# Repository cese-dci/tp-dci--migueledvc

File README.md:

#tp-dci--migueledvc

Placa adaptadora de señales de radar
====================================

+ El presente documento presenta la idea de un circuito adaptador de señales típicas de un radar.

+ No se especifica un modelo de radar en particular.

+ El circuíto es parte del desarrollo de un procesador de radar con tecnología FPGA-SoC. (ADC-SoC de Terasic)

+ Se utiliza para esta placa licencia "BSD 3-clause"

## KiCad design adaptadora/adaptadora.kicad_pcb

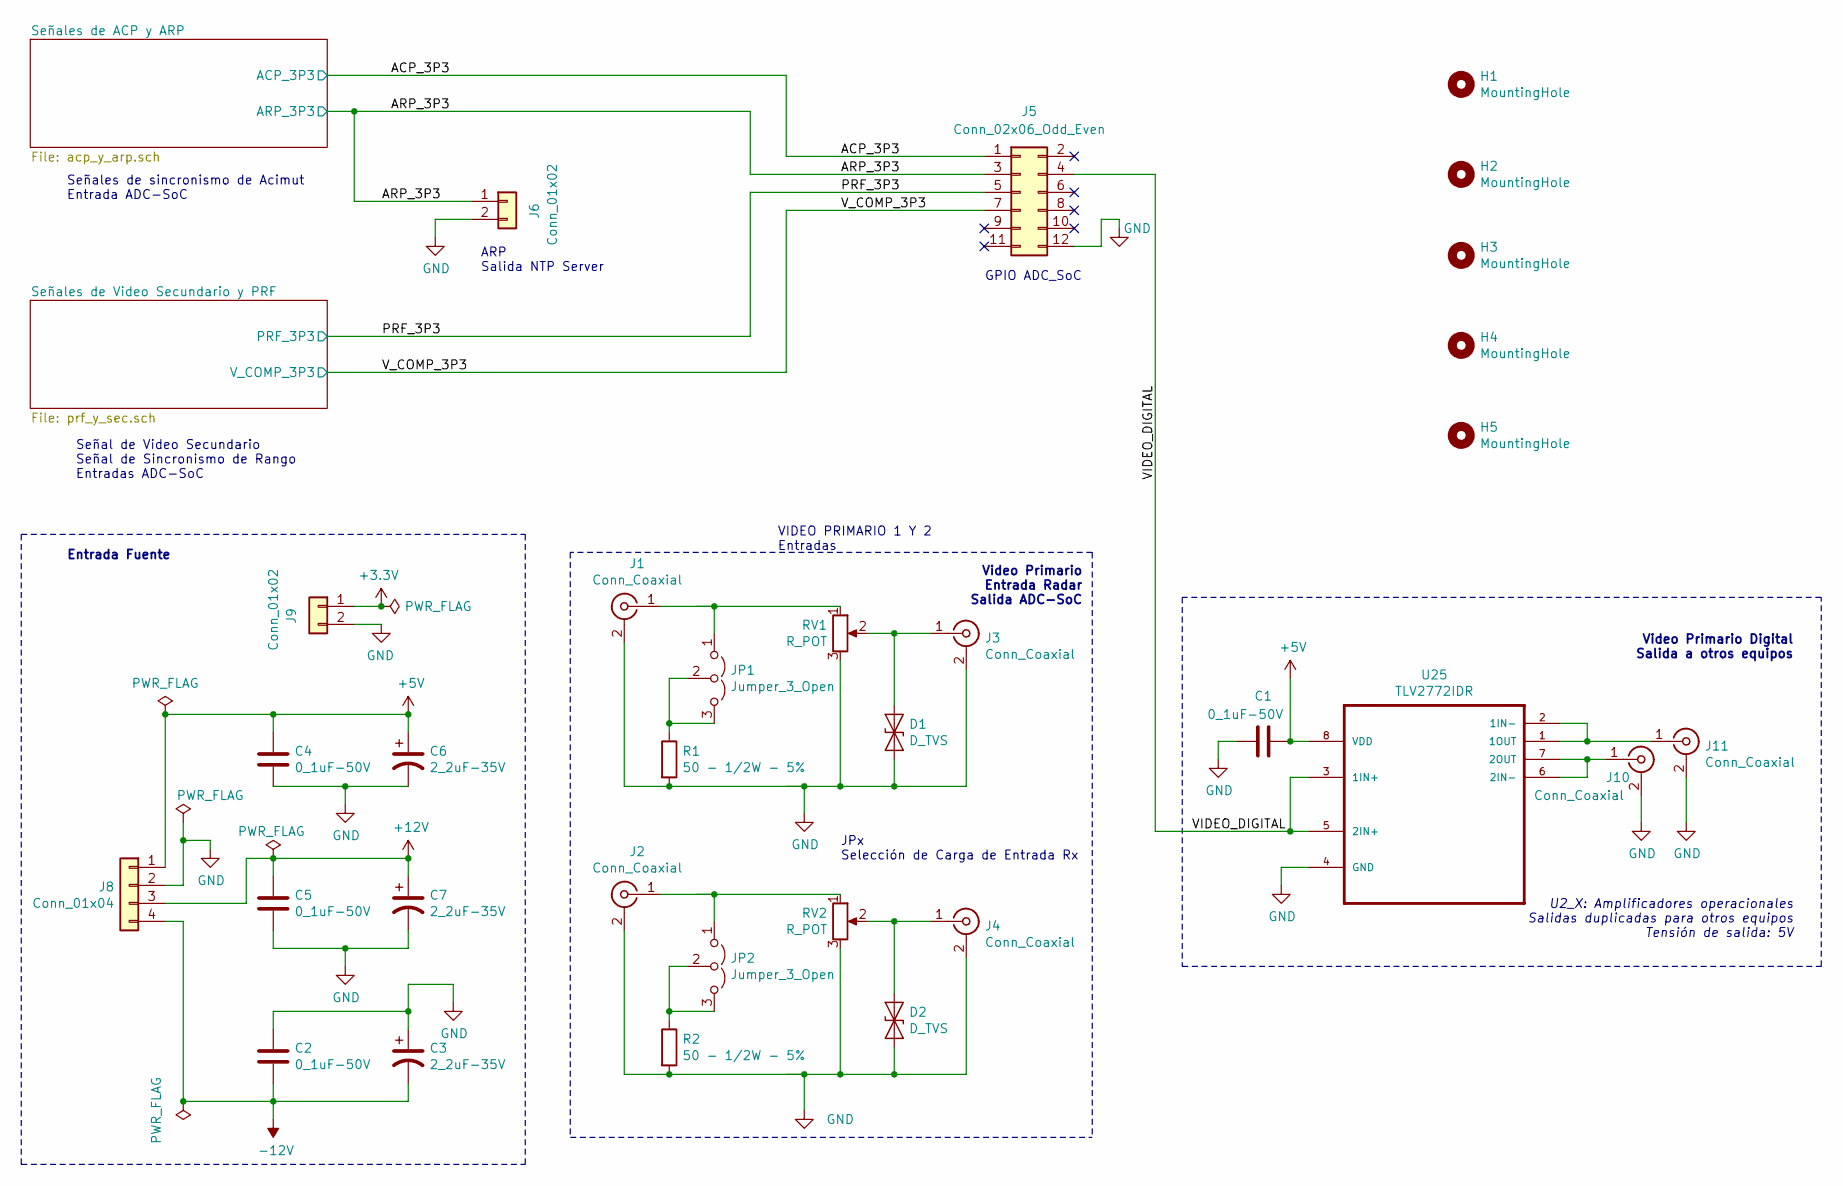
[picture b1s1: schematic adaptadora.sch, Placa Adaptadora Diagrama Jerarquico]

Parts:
C1, C2, C4, C5: 0_1uF-50V; C_0805_2012Metric
C3, C6, C7: 2_2uF-35V; CP_EIA-6032-28_Kemet-C
D1, D2: D_TVS; D_DO-15_P10.16mm_Horizontal
H1, H2, H3, H4, H5: MountingHole; MountingHole_3.2mm_M3_Pad
J1, J2, J3, J4, J10, J11: Conn_Coaxial; SMA_Amphenol_901-144_Vertical
J5: Conn_02x06_Odd_Even; PinHeader_2x06_P2.54mm_Horizontal
J6, J9: Conn_01x02; PinHeader_1x02_P2.54mm_Vertical
J8: Conn_01x04; PinHeader_1x04_P2.54mm_Vertical
JP1, JP2: Jumper_3_Open; PinHeader_1x03_P2.54mm_Vertical
R1, R2: 50 - 1/2W - 5%; R_Axial_DIN0414_L11.9mm_D4.5mm_P15.24mm_Horizontal
RV1, RV2: R_POT; Potentiometer_Bourns_3296W_Vertical
U25: TLV2772IDR; SOIC-8_3.9x4.9mm_P1.27mm

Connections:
+3V3: J9.1; also elsewhere on the board
+5V: C1.1, C4.1, C6.1, J8.1, U25.8 (VDD); also elsewhere on the board
+12V: C5.1, C7.1, J8.3; also elsewhere on the board
-12V: C2.2, C3.2, J8.4; also elsewhere on the board
/ACP_3P3: J5.9; also elsewhere on the board
/PRF_3P3: J5.5; also elsewhere on the board
GND: C1.2, C2.1, C3.1, C4.2, C5.2, C6.2, C7.2, D1.2 (A2), D2.2 (A2), J1.2 (Ext), J2.2 (Ext), J3.2 (Ext), J4.2 (Ext), J5.12, J6.2, J8.2, J9.2, J10.2 (Ext), J11.2 (Ext), R1.2, R2.2, RV1.3, RV2.3, U25.4 (GND); also elsewhere on the board
unnamed: D1.1 (A1), J3.1 (In), RV1.2
unnamed: D2.1 (A1), J4.1 (In), RV2.2
unnamed: J1.1 (In), JP1.1 (A), RV1.1
unnamed: J2.1 (In), JP2.1 (A), RV2.1
unnamed: J10.1 (In), U25.6 (2IN-), U25.7 (2OUT)
unnamed: J11.1 (In), U25.1 (1OUT), U25.2 (1IN-)
unnamed: JP1.2 (C), JP1.3 (B), R1.1
unnamed: JP2.2 (C), JP2.3 (B), R2.1

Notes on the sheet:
VIDEO PRIMARIO 1 Y 2 Entradas
Video Primario Entrada Radar Salida ADC-SoC
Señales de sincronismo de Acimut Entrada ADC-SoC
GPIO ADC_SoC
ARP Salida NTP Server
Video Primario Digital Salida a otros equipos
Entrada Fuente
Señal de Video Secundario Señal de Sincronismo de Rango Entradas ADC-SoC
U2_X: Amplificadores operacionales Salidas duplicadas para otros equipos Tensión de salida: 5V
JPx Selección de Carga de Entrada Rx

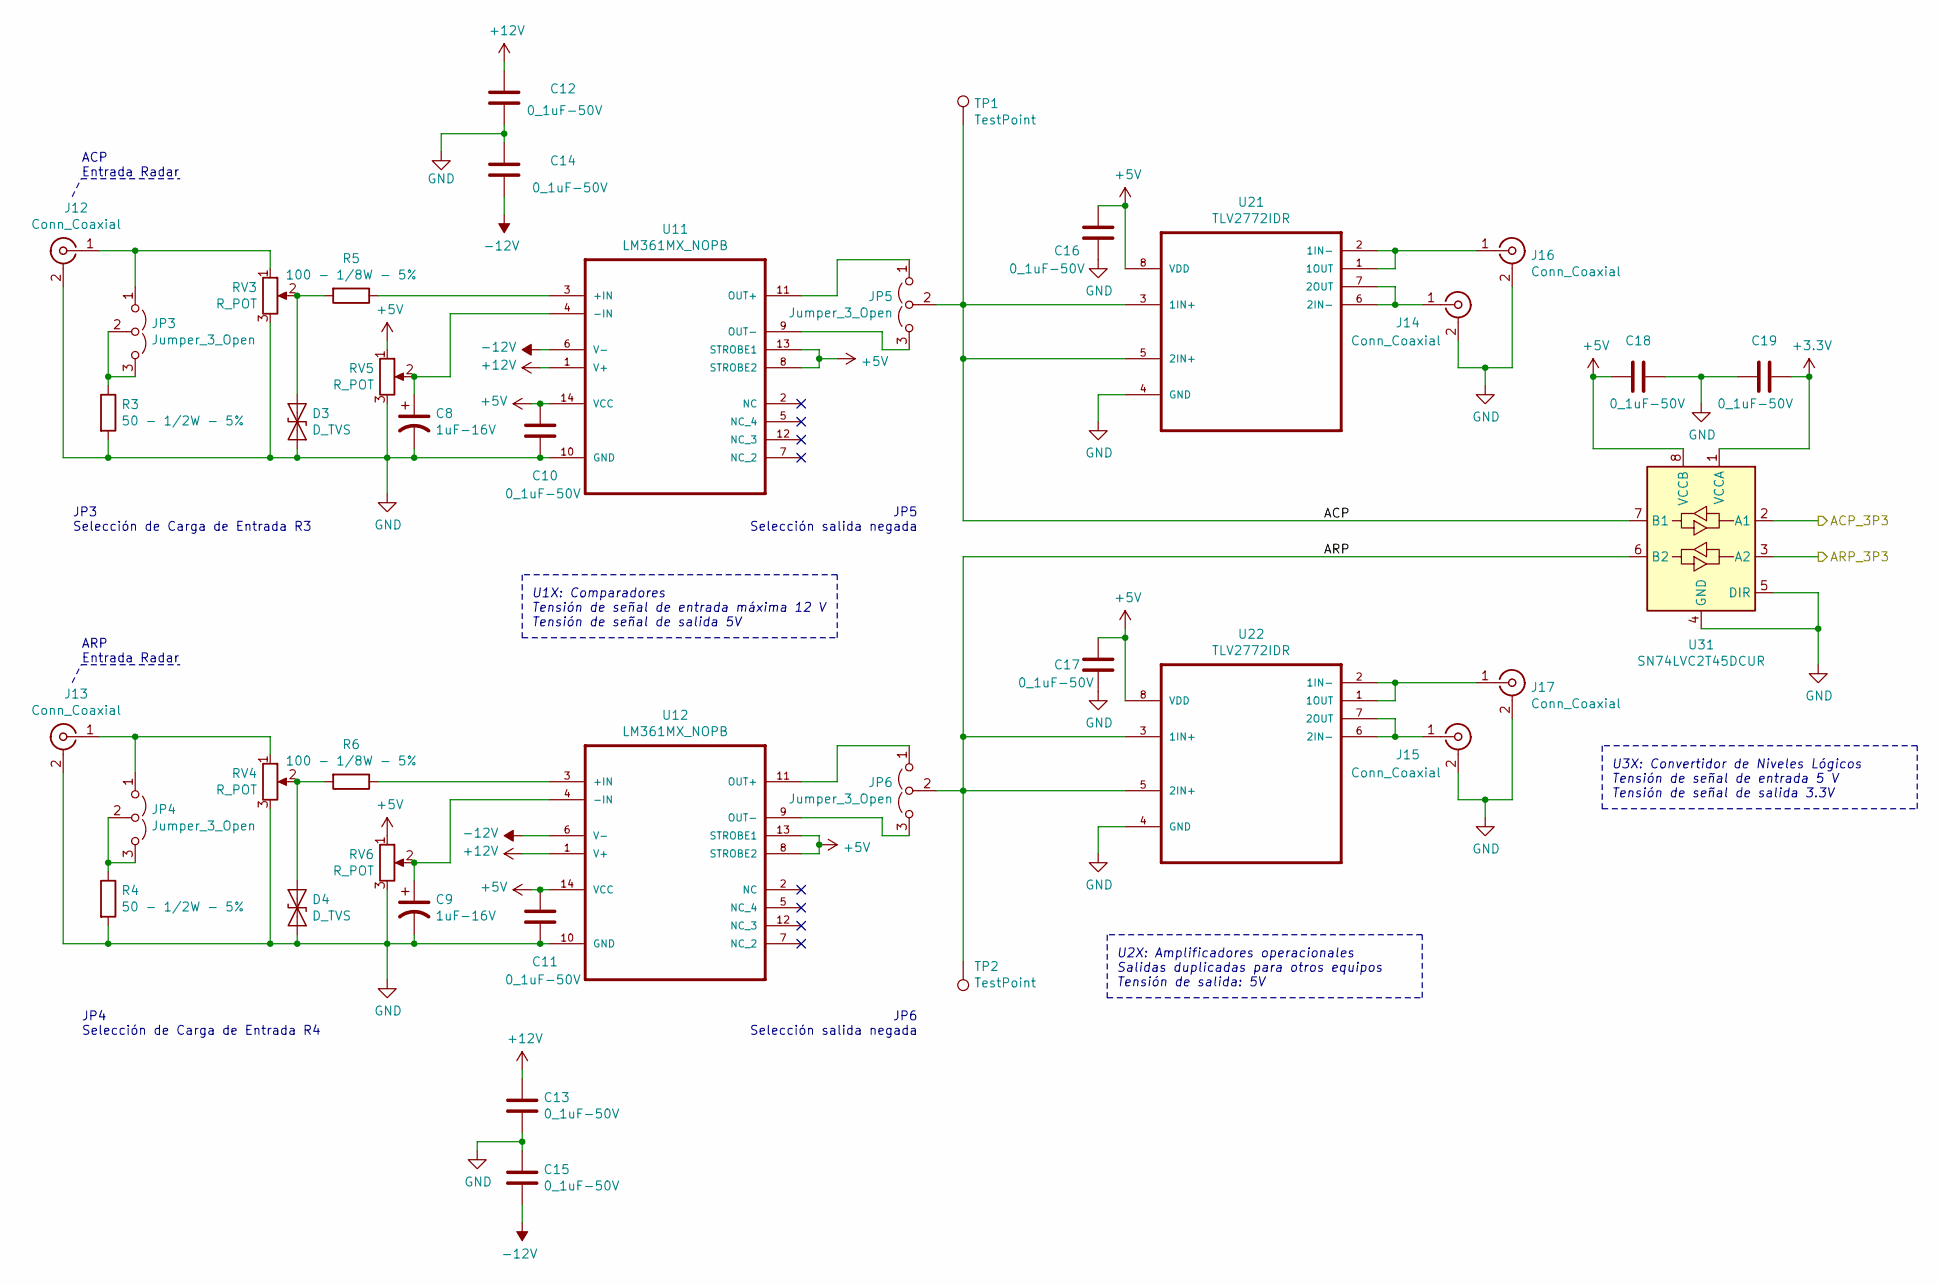
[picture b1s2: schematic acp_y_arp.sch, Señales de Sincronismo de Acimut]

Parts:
C8, C9: 1uF-16V; R_1206_3216Metric
C10, C11, C12, C13, C14, C15, C16, C17, C18, C19: 0_1uF-50V; C_0805_2012Metric
D3, D4: D_TVS; D_DO-15_P10.16mm_Horizontal
J12, J13, J14, J15, J16, J17: Conn_Coaxial; SMA_Amphenol_901-144_Vertical
JP3, JP4, JP5, JP6: Jumper_3_Open; PinHeader_1x03_P2.54mm_Vertical
R3, R4: 50 - 1/2W - 5%; R_Axial_DIN0414_L11.9mm_D4.5mm_P15.24mm_Horizontal
R5, R6: 100 - 1/8W - 5%; R_0805_2012Metric
RV3, RV4, RV5, RV6: R_POT; Potentiometer_Bourns_3296W_Vertical
TP1, TP2: TestPoint; TestPoint_THTPad_1.5x1.5mm_Drill0.7mm
U11, U12: LM361MX_NOPB; DIP-14_W7.62mm_Socket
U21, U22: TLV2772IDR; SOIC-8_3.9x4.9mm_P1.27mm
U31: SN74LVC2T45DCUR; VSSOP-8_2.4x2.1mm_P0.5mm

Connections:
+3V3: C19.1, U31.1 (VCCA); also elsewhere on the board
+5V: C10.2, C11.2, C16.1, C17.1, C18.2, RV5.1, RV6.1, U11.8 (STROBE2), U11.13 (STROBE1), U11.14 (VCC), U12.8 (STROBE2), U12.13 (STROBE1), U12.14 (VCC), U21.8 (VDD), U22.8 (VDD), U31.8 (VCCB); also elsewhere on the board
+12V: C12.1, C13.1, U11.1 (V+), U12.1 (V+); also elsewhere on the board
-12V: C14.2, C15.2, U11.6 (V-), U12.6 (V-); also elsewhere on the board
/ACP_3P3: U31.2 (A1); also elsewhere on the board
/Señales de ACP y ARP/ACP: JP5.2 (C), TP1.1, U21.3 (1IN+), U21.5 (2IN+), U31.7 (B1)
/Señales de ACP y ARP/ARP: JP6.2 (C), TP2.1, U22.3 (1IN+), U22.5 (2IN+), U31.6 (B2)
GND: C8.2, C9.2, C10.1, C11.1, C12.2, C13.2, C14.1, C15.1, C16.2, C17.2, C18.1, C19.2, D3.2 (A2), D4.2 (A2), J12.2 (Ext), J13.2 (Ext), J14.2 (Ext), J15.2 (Ext), J16.2 (Ext), J17.2 (Ext), R3.2, R4.2, RV3.3, RV4.3, RV5.3, RV6.3, U11.10 (GND), U12.10 (GND), U21.4 (GND), U22.4 (GND), U31.4 (GND), U31.5 (DIR); also elsewhere on the board
unnamed: C8.1, RV5.2, U11.4 (-IN)
unnamed: C9.1, RV6.2, U12.4 (-IN)
unnamed: D3.1 (A1), R5.2, RV3.2
unnamed: D4.1 (A1), R6.2, RV4.2
unnamed: J12.1 (In), JP3.1 (A), RV3.1
unnamed: J13.1 (In), JP4.1 (A), RV4.1
unnamed: J14.1 (In), U21.6 (2IN-), U21.7 (2OUT)
unnamed: J15.1 (In), U22.6 (2IN-), U22.7 (2OUT)
unnamed: J16.1 (In), U21.1 (1OUT), U21.2 (1IN-)
unnamed: J17.1 (In), U22.1 (1OUT), U22.2 (1IN-)
unnamed: JP3.2 (C), JP3.3 (B), R3.1
unnamed: JP4.2 (C), JP4.3 (B), R4.1
unnamed: JP5.1 (A), U11.11 (OUT+)
unnamed: JP5.3 (B), U11.9 (OUT-)
unnamed: JP6.1 (A), U12.11 (OUT+)
unnamed: JP6.3 (B), U12.9 (OUT-)
unnamed: R5.1, U11.3 (+IN)
unnamed: R6.1, U12.3 (+IN)

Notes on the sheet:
ACP Entrada Radar
ARP Entrada Radar
U1X: Comparadores Tensión de señal de entrada máxima 12 V Tensión de señal de salida 5V
U2X: Amplificadores operacionales Salidas duplicadas para otros equipos Tensión de salida: 5V
U3X: Convertidor de Niveles Lógicos Tensión de señal de entrada 5 V Tensión de señal de salida 3.3V
JP3 Selección de Carga de Entrada R3
JP4 Selección de Carga de Entrada R4
JP5 Selección salida negada
JP6 Selección salida negada

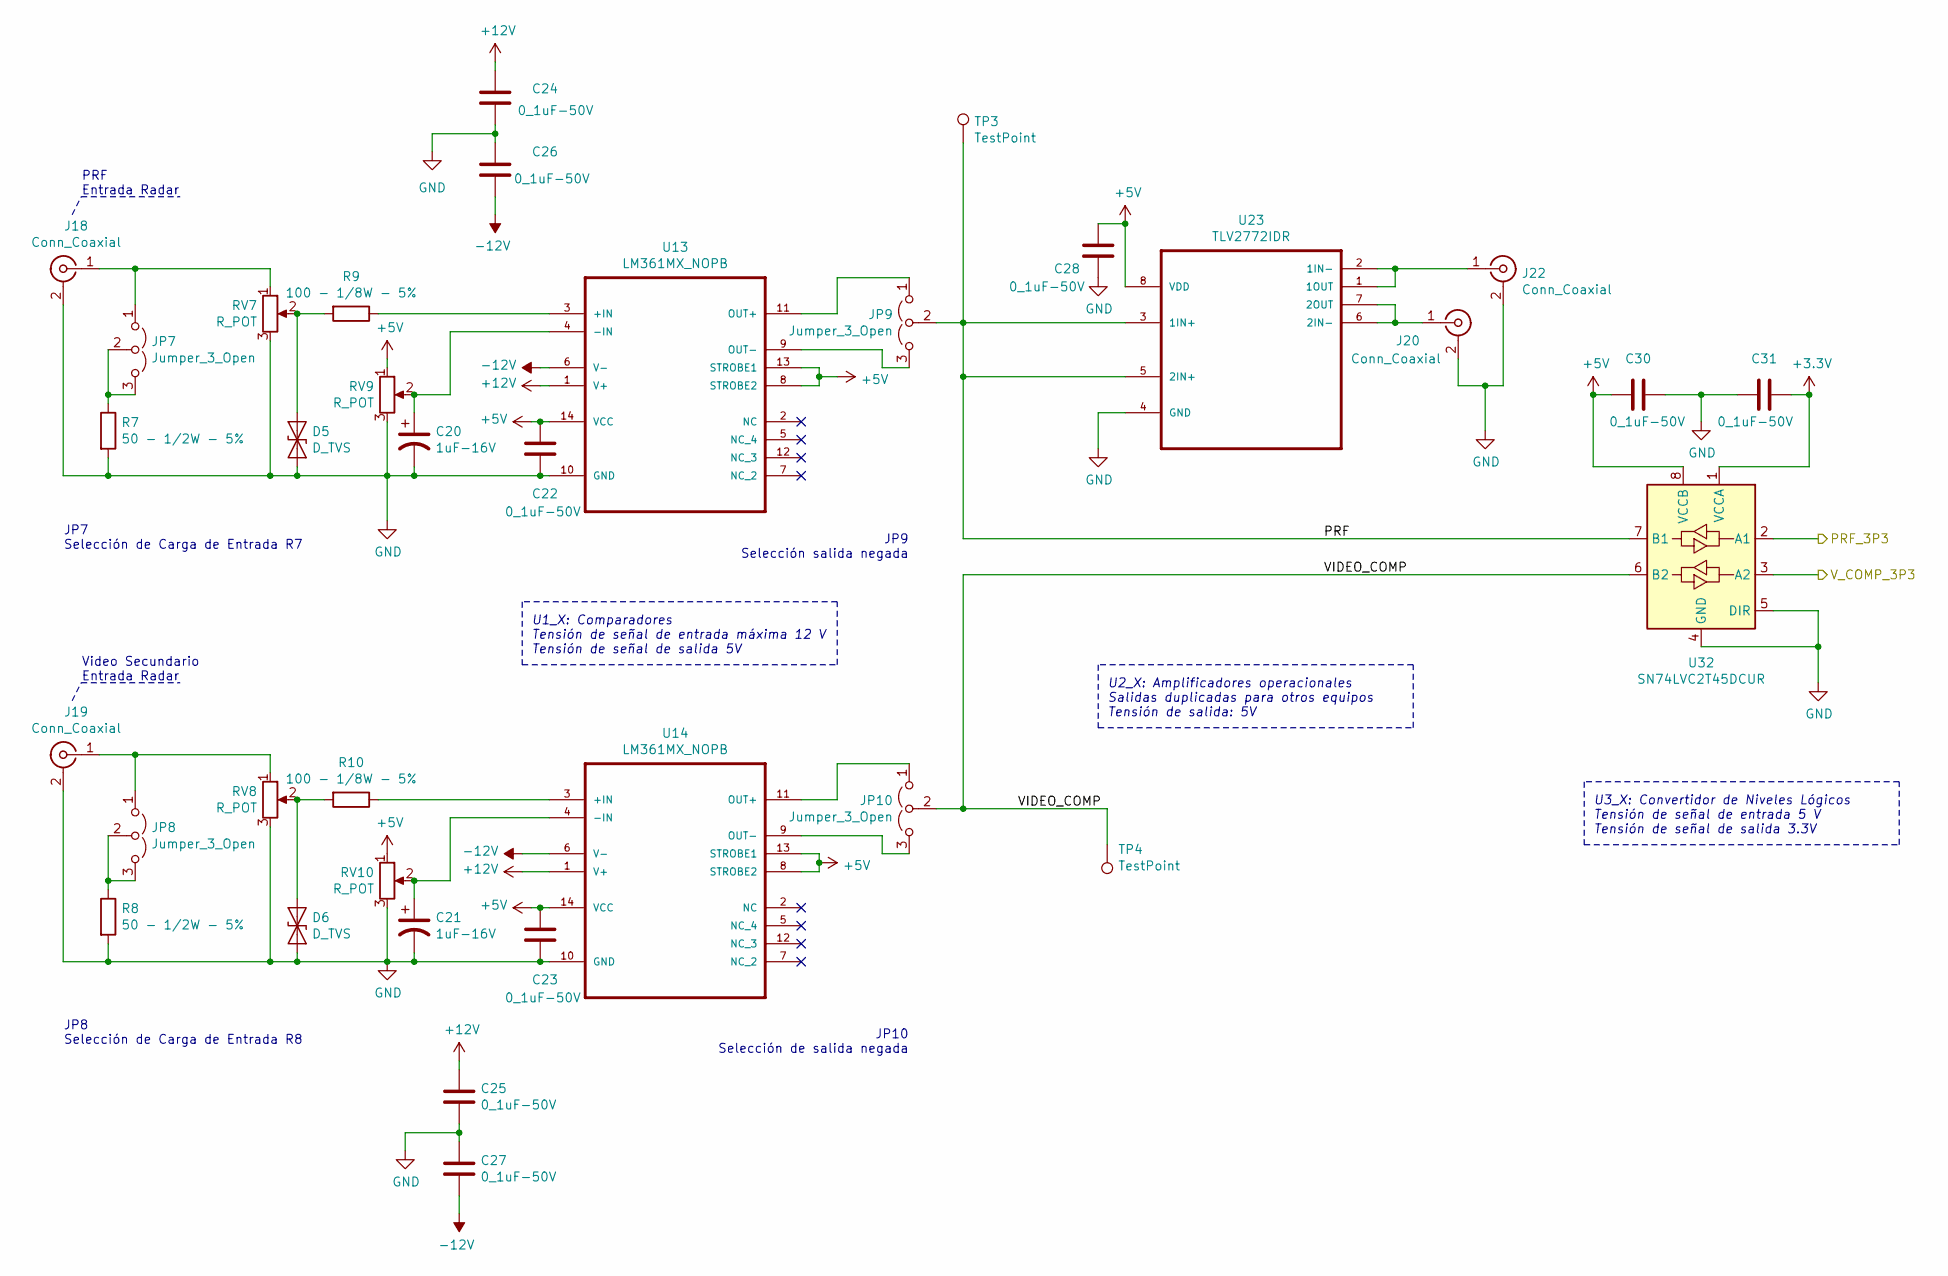
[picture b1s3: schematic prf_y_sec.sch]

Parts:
C20, C21: 1uF-16V; R_1206_3216Metric
C22, C23, C24, C25, C26, C27, C28, C30, C31: 0_1uF-50V; C_0805_2012Metric
D5, D6: D_TVS; D_DO-15_P10.16mm_Horizontal
J18, J19, J20, J22: Conn_Coaxial; SMA_Amphenol_901-144_Vertical
JP7, JP8, JP9, JP10: Jumper_3_Open; PinHeader_1x03_P2.54mm_Vertical
R7, R8: 50 - 1/2W - 5%; R_Axial_DIN0414_L11.9mm_D4.5mm_P15.24mm_Horizontal
R9, R10: 100 - 1/8W - 5%; R_0805_2012Metric
RV7, RV8, RV9, RV10: R_POT; Potentiometer_Bourns_3296W_Vertical
TP3, TP4: TestPoint; TestPoint_THTPad_1.5x1.5mm_Drill0.7mm
U13, U14: LM361MX_NOPB; DIP-14_W7.62mm_Socket
U23: TLV2772IDR; SOIC-8_3.9x4.9mm_P1.27mm
U32: SN74LVC2T45DCUR; VSSOP-8_2.4x2.1mm_P0.5mm

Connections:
+3V3: C31.1, U32.1 (VCCA); also elsewhere on the board
+5V: C22.2, C23.2, C28.1, C30.2, RV9.1, RV10.1, U13.8 (STROBE2), U13.13 (STROBE1), U13.14 (VCC), U14.8 (STROBE2), U14.13 (STROBE1), U14.14 (VCC), U23.8 (VDD), U32.8 (VCCB); also elsewhere on the board
+12V: C24.1, C25.1, U13.1 (V+), U14.1 (V+); also elsewhere on the board
-12V: C26.2, C27.2, U13.6 (V-), U14.6 (V-); also elsewhere on the board
/PRF_3P3: U32.2 (A1); also elsewhere on the board
/Señales de Video Secundario y PRF/PRF: JP9.2 (C), TP3.1, U23.3 (1IN+), U23.5 (2IN+), U32.7 (B1)
/Señales de Video Secundario y PRF/VIDEO_COMP: JP10.2 (C), TP4.1, U32.6 (B2)
GND: C20.2, C21.2, C22.1, C23.1, C24.2, C25.2, C26.1, C27.1, C28.2, C30.1, C31.2, D5.2 (A2), D6.2 (A2), J18.2 (Ext), J19.2 (Ext), J20.2 (Ext), J22.2 (Ext), R7.2, R8.2, RV7.3, RV8.3, RV9.3, RV10.3, U13.10 (GND), U14.10 (GND), U23.4 (GND), U32.4 (GND), U32.5 (DIR); also elsewhere on the board
unnamed: C20.1, RV9.2, U13.4 (-IN)
unnamed: C21.1, RV10.2, U14.4 (-IN)
unnamed: D5.1 (A1), R9.2, RV7.2
unnamed: D6.1 (A1), R10.2, RV8.2
unnamed: J18.1 (In), JP7.1 (A), RV7.1
unnamed: J19.1 (In), JP8.1 (A), RV8.1
unnamed: J20.1 (In), U23.6 (2IN-), U23.7 (2OUT)
unnamed: J22.1 (In), U23.1 (1OUT), U23.2 (1IN-)
unnamed: JP7.2 (C), JP7.3 (B), R7.1
unnamed: JP8.2 (C), JP8.3 (B), R8.1
unnamed: JP9.1 (A), U13.11 (OUT+)
unnamed: JP9.3 (B), U13.9 (OUT-)
unnamed: JP10.1 (A), U14.11 (OUT+)
unnamed: JP10.3 (B), U14.9 (OUT-)
unnamed: R9.1, U13.3 (+IN)
unnamed: R10.1, U14.3 (+IN)

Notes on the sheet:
PRF Entrada Radar
Video Secundario Entrada Radar
U1_X: Comparadores Tensión de señal de entrada máxima 12 V Tensión de señal de salida 5V
U2_X: Amplificadores operacionales Salidas duplicadas para otros equipos Tensión de salida: 5V
U3_X: Convertidor de Niveles Lógicos Tensión de señal de entrada 5 V Tensión de señal de salida 3.3V
JP7 Selección de Carga de Entrada R7
JP8 Selección de Carga de Entrada R8
JP9 Selección salida negada
JP10 Selección de salida negada

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
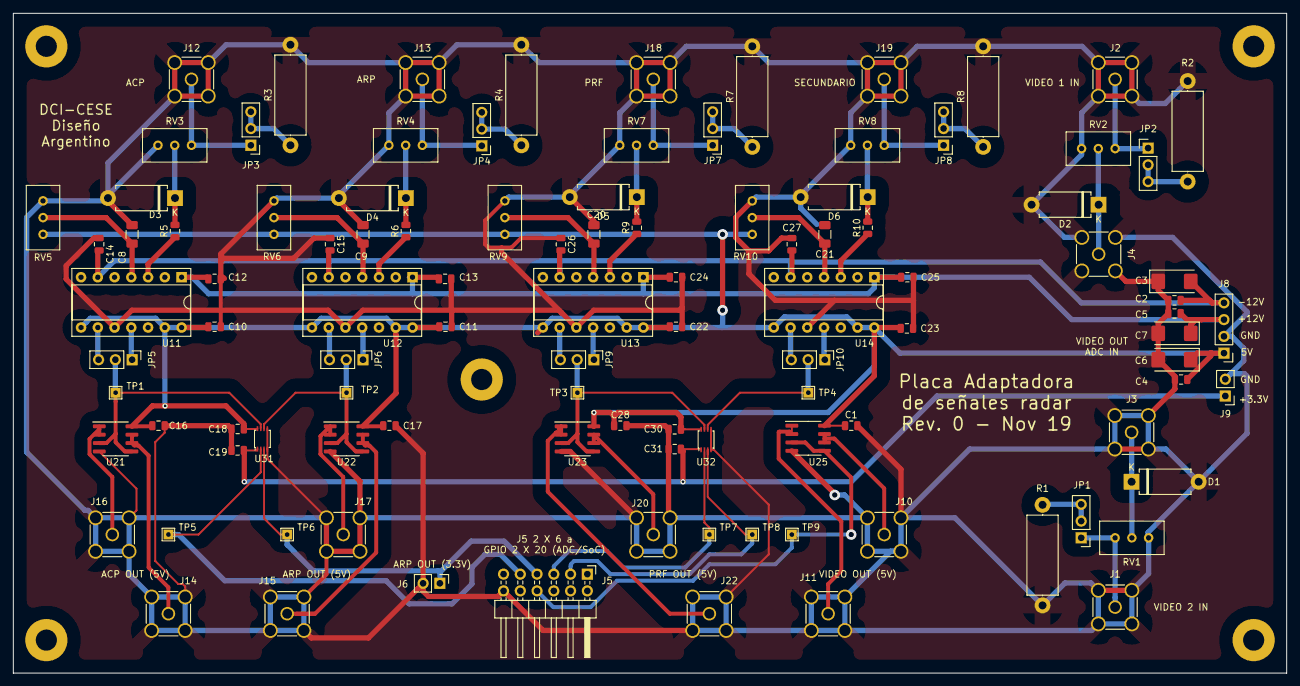
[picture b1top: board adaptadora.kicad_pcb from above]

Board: 2 copper layers, 193.0 x 100.0 mm, 110 parts (0 on the bottom side), 56 nets.

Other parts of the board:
TP5, TP6, TP7, TP8, TP9: TestPoint; TestPoint_THTPad_1.5x1.5mm_Drill0.7mm

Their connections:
/ACP_3P3: TP5.1; also elsewhere on the board
/PRF_3P3: TP7.1; also elsewhere on the board

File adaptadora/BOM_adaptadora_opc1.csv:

Id;Identificador;Empaquetado;Cantidad;Identificación;Suministrador y ref
1;H5,H4,H3,H2,H1;MountingHole_3.2mm_M3_Pad;5;MountingHole;
2;REF**;KiCad-Logo2_5mm_Copper;1;KiCad-Logo2_5mm_Copper;
3;JP1,JP2,JP3,JP4,JP5,JP6,JP7,JP8,JP9,JP10;SolderJumper-3_P1.3mm_Open_Pad1.0x1.5mm_NumberLabels;10;Jumper_3_Open;
4;J1,J11,J10,J19,J12,J13,J18,J2,J3,J4,J14,J15,J16,J17,J20,J22;SMA_Amphenol_901-144_Vertical;16;Conn_Coaxial;
5;D6,D5,D4,D3,D2,D1;D_0201_0603Metric;6;D_TVS;
6;R4,R8,R3,R1,R7,R2;R_Axial_DIN0414_L11.9mm_D4.5mm_P15.24mm_Horizontal;6;50 - 1/2W - 5%;
7;U25,U23,U22,U21;SOIC-8_3.9x4.9mm_P1.27mm;4;TLV2772IDR;
8;U14,U13,U12,U11;SOIC-14_3.9x8.7mm_P1.27mm;4;LM361MX_NOPB;
9;C1,C2,C4,C5,C10,C11,C12,C13,C14,C15,C16,C17,C18,C19,C22,C23,C24,C25,C26,C27,C28,C30,C31;C_0805_2012Metric;23;0.1uF-50V;
10;C3,C6,C7;CP_EIA-6032-28_Kemet-C;3;2.2uF-35V;
11;C8,C9,C20,C21;R_1206_3216Metric;4;1uF-16V;
12;J5;PinHeader_2x20_P2.54mm_Horizontal;1;Conn_02x20_Odd_Even;
13;J6,J9;PinHeader_1x02_P2.54mm_Vertical;2;Conn_01x02;
14;J7;PinHeader_2x20_P2.00mm_Vertical;1;Conn_02x20_Odd_Even;
15;J8;PinHeader_1x04_P2.54mm_Vertical;1;Conn_01x04;
16;R5,R6,R9,R10;R_0805_2012Metric;4;100 - 1/8W - 5%;
17;RV1,RV2,RV3,RV4,RV5,RV6,RV7,RV8,RV9,RV10;Potentiometer_Bourns_3296W_Vertical;10;R_POT;
18;TP1,TP2,TP3,TP4;TestPoint_THTPad_1.5x1.5mm_Drill0.7mm;4;TestPoint;
19;U31,U32;VSSOP-8_2.4x2.1mm_P0.5mm;2;SN74LVC2T45DCUR;

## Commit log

2019-10-10 add files
2019-10-11 add files, libs, sch videos, sch sincronismo
2019-10-18 esquemático terminado faltan valores
2019-10-18 se enumeraron componentes faltan valores
2019-10-18 se agregan valores, etiquetas jerarquicas y poligonos
2019-10-18 se agrega texto
2019-10-18 en proceso de checkeo ERC
2019-10-18 esquemático corregido por compañero
2019-10-19 se agrega pdf
2019-10-25 work in progress
2019-10-25 correcciones implementadas
2019-10-26 se agregan huellas, en progreso
2019-10-31 pcb work in progress
2019-11-01 Componentes acomodados en PCB
2019-11-01 Se dibuja borde de placa
2019-11-01 correcciones y archivos agregados
2019-11-01 archivos agregados
2019-11-01 pcb, work in progress
2019-11-02 pcb en proceso de diseño
2019-11-07 add SMA 901-143 3d model
2019-11-07 esq y pcb work in progress
2019-11-07 add SMA 3D model & img
2019-11-08 mejorando BOM - work in progress
2019-11-08 se ordenan campos de integrados
2019-11-16 agrego modelo 3d lm361 sobre el sócalo
2019-11-16 se cambia footprint de componentes y el posicionamiento
2019-11-16 creo librerías de huellas y modelos 3D
2019-11-17 ruteo en proceso
2019-11-18 ultimo commit antes de quitar dac del esq
2019-11-18 se quita el gpio 2x20 por un 2x6
2019-11-19 se agrega planos de tierra
2019-11-22 modificaciones bom
2019-11-22 add ibom & img's
2019-11-23 se suben nuevamente
2019-11-23 se cambian rutas de modelos 3D y se sube .step de sma vert
